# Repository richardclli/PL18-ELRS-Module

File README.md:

[English](README.md) | [中文](README_CN.md)

# Flysky PL18 ExpressLRS TX Module

A DIY internal ExpressLRS transmitter module for the Flysky Paladin PL18 radio, repurposing the stock FRM301 module's casing and RF module.

## Overview

The Flysky PL18 ships with the FRM301 external TX module. This project replaces the FRM301's internal PCB with a custom carrier board that combines a **Waveshare ESP32-S3-Tiny** as the protocol bridge and the FRM301's **HF200 RF module** as the 2.4GHz ExpressLRS frontend. The result is a fully-featured, drop-in ExpressLRS transmitter module that fits the existing module bay and communicates with the radio over its 5-pin SPORT port.

### Features

- Drop-in replacement for the FRM301 module — reuses the original casing
- Waveshare ESP32-S3-Tiny running ExpressLRS firmware
- HF200 2.4GHz RF module with antenna diversity switching
- Dual WS2812B-2020 RGB status LEDs
- Boot button for easy firmware flashing
- Powered entirely from the radio's 5V rail

## Photos

## Bill of Materials

| Ref | Part | Qty | Notes |
|-----|------|:---:|-------|
| — | PL18-ELRS PCB | 1 | Order using the Gerber files in this repo |
| — | FRM301 donor module | 1 | Harvest the HF200 RF module and the plastic casing |
| U1 | Waveshare ESP32-S3-Tiny | 1 | [Product page](https://www.waveshare.com/esp32-s3-tiny.htm) |
| U2 | HF200 RF module | 1 | Desoldered from the FRM301 |
| D1, D2 | WS2812B-2020 | 2 | 2.0×2.0mm PLCC4 package RGB LED |
| R1, R2 | 10kΩ 0603 resistor | 2 | |
| SW1 | KMR2 tactile switch | 1 | 3.2×4.2mm |
| J1 | 5-pin 2.54mm male header | 1 | DS-B01F-A-S2 or equivalent |

## Pinout

### PL18 Connector (J1)

| Pin | Signal | ESP32-S3 GPIO | Description |
|:---:|:------:|:-------------:|-------------|
| 1 | SPORT | IO04 | S.Port (bidirectional CRSF protocol) |
| 2 | GND | — | Ground |
| 3 | +5V | — | 5V power input from radio |
| 4 | NC | — | Not connected |
| 5 | NC | — | Not connected |

### ESP32-S3 to HF200 RF Module

| ESP32-S3 GPIO | HF200 Pin | Function |
|:-------------:|:---------:|----------|
| IO04 | — | SPORT (to PL18 connector) |
| IO06 | TXEN | TX enable |
| IO07 | RXEN | RX enable |
| IO08 | DI01 | Bidirectional data |
| IO09 | BUSY | Busy status (input) |
| IO10 | SPI_NSS | SPI chip select |
| IO11 | SPI_MOSI | SPI MOSI |
| IO12 | SPI_CLK | SPI clock |
| IO13 | SPI_MISO | SPI MISO |
| IO14 | RESET | HF200 reset |
| IO15 | L_ANT_SW | Left antenna switch |
| IO16 | R_ANT_SW | Right antenna switch |
| IO17 | SW1 | Boot button (active low) |
| IO18 | D1 DIN | WS2812B LED data line |

### Power

| Rail | Source | Supplies |
|------|--------|----------|
| +5V | PL18 connector (J1) | ESP32-S3-Tiny (U1), HF200 (U2) |
| +3V3 | ESP32-S3 internal regulator | WS2812B LEDs (D1, D2), L_POWER pull-up (R2) |

## Schematic & PCB

The PCB design was created in **KiCad 10.0**.

- **Layers:** 2-layer FR4, 1.6mm thickness
- **Copper:** 35μm (1oz)
- **Surface finish:** HASL or ENIG
- **Board shape:** Custom outline matching the FRM301 internal cavity

### KiCad project files

| File | Description |
|------|-------------|
| `PL18_ELRS.kicad_pro` | KiCad project file |
| `PL18_ELRS.kicad_sch` | Schematic |
| `PL18_ELRS.kicad_pcb` | PCB layout |
| `Multi.kicad_sym` | Custom symbol library |
| `Multi.pretty/` | Custom footprint library |

The custom footprints include the `WS_ESP32S3_Tiny` (23-pin SMT module) and `HF200-SMT` (22-pin RF module) footprints matched to the donor parts.

## Assembly

1. **Harvest the HF200.** Open the FRM301 module and carefully desolder the HF200 RF module from the original PCB. Set the plastic casing aside for later use.
2. **Solder the HF200 (U2).** Mount the HF200 module on the **back side** of the PL18-ELRS PCB at the U2 footprint.
3. **Solder the ESP32-S3-Tiny (U1).** Mount on the **front side** at the U1 footprint.
4. **Solder passives and LEDs.** Place R1, R2 (10kΩ 0603), D1, D2 (WS2812B-2020), and SW1 (KMR2 switch) on the **front side**.
5. **Solder the header (J1).** Mount the 5-pin male header on the **back side**, ensuring the pins face toward the rear of the module for proper alignment with the PL18 bay connector.
6. **Fit into the casing.** Insert the assembled PCB into the salvaged FRM301 plastic casing.

## Firmware

The ExpressLRS target definition for the Flysky PL18 is maintained at:

**[github.com/richardclli/ELRS-targets](https://github.com/richardclli/ELRS-targets)**

### Flashing

1. Use the ExpressLRS Configurator and select the **Flysky PL18** target.
2. Connect the ESP32-S3-Tiny via USB to your computer.
3. Hold the boot button (SW1) while applying power (or while connecting USB).
4. Flash the firmware using the configurator.

After flashing, configure ExpressLRS to use the **SPORT** protocol for telemetry.

## Manufacturing

The repository includes a complete set of manufacturing outputs in the root directory:

| File | Description |
|------|-------------|
| `PL18_ELRS-F_Cu.gbr` | Top copper |
| `PL18_ELRS-B_Cu.gbr` | Bottom copper |
| `PL18_ELRS-F_Mask.gbr` | Top solder mask |
| `PL18_ELRS-B_Mask.gbr` | Bottom solder mask |
| `PL18_ELRS-F_Paste.gbr` | Top solder paste |
| `PL18_ELRS-B_Paste.gbr` | Bottom solder paste |
| `PL18_ELRS-F_Silkscreen.gbr` | Top silkscreen |
| `PL18_ELRS-B_Silkscreen.gbr` | Bottom silkscreen |
| `PL18_ELRS-Edge_Cuts.gbr` | Board outline |
| `PL18_ELRS-PTH.drl` | Plated through-hole drill |
| `PL18_ELRS-NPTH.drl` | Non-plated through-hole drill |

To order PCBs, zip all Gerber and drill files and upload to your preferred fab (JLCPCB, PCBWay, etc.) with these specs:

- **Layers:** 2
- **Thickness:** 1.6mm
- **Material:** FR4
- **Copper:** 1oz
- **Surface finish:** HASL (or ENIG for easier hand-soldering)

## License

This project is licensed under the **MIT License** — see the [LICENSE](LICENSE) file for details.

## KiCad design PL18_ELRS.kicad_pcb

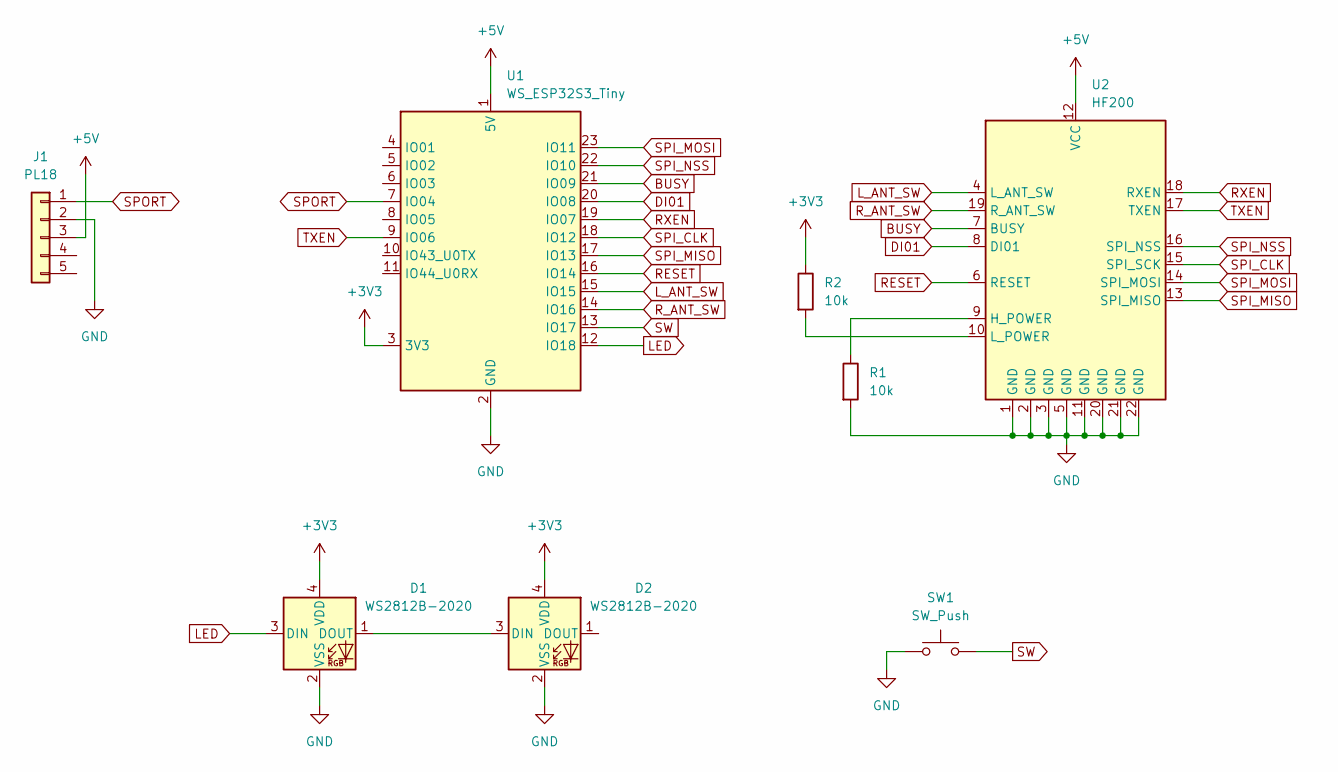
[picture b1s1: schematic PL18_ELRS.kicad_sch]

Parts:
D1, D2: WS2812B-2020; LED_WS2812B-2020_PLCC4_2.0x2.0mm
J1: PL18; DS-B01F-A-S2
R1, R2: 10k; R_0603_1608Metric_Pad0.98x0.95mm_HandSolder
SW1: SW_Push; SW_Push_3.2x4.2
U1: WS_ESP32S3_Tiny
U2: HF200; HF200-SMT

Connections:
+3V3: D1.4 (VDD), D2.4 (VDD), R2.1, U1.3 (3V3)
+5V: J1.3, U1.1 (5V), U2.12 (VCC)
BUSY: U1.21 (IO09), U2.7 (BUSY)
DI01: U1.20 (IO08), U2.8 (DI01)
GND: D1.2 (VSS), D2.2 (VSS), J1.2, R1.2, SW1.1, U1.2 (GND), U2.1 (GND), U2.2 (GND), U2.3 (GND), U2.5 (GND), U2.11 (GND), U2.20 (GND), U2.21 (GND), U2.22 (GND)
LED: D1.3 (DIN), U1.12 (IO18)
L_ANT_SW: U1.15 (IO15), U2.4 (L_ANT_SW)
unnamed: D1.1 (DOUT), D2.3 (DIN)
unnamed: R1.1, U2.9 (H_POWER)
unnamed: R2.2, U2.10 (L_POWER)
RESET: U1.16 (IO14), U2.6 (RESET)
RXEN: U1.19 (IO07), U2.18 (RXEN)
R_ANT_SW: U1.14 (IO16), U2.19 (R_ANT_SW)
SPI_CLK: U1.18 (IO12), U2.15 (SPI_SCK)
SPI_MISO: U1.17 (IO13), U2.13 (SPI_MISO)
SPI_MOSI: U1.23 (IO11), U2.14 (SPI_MOSI)
SPI_NSS: U1.22 (IO10), U2.16 (SPI_NSS)
SPORT: J1.1, U1.7 (IO04)
SW: SW1.2, U1.13 (IO17)
TXEN: U1.9 (IO06), U2.17 (TXEN)

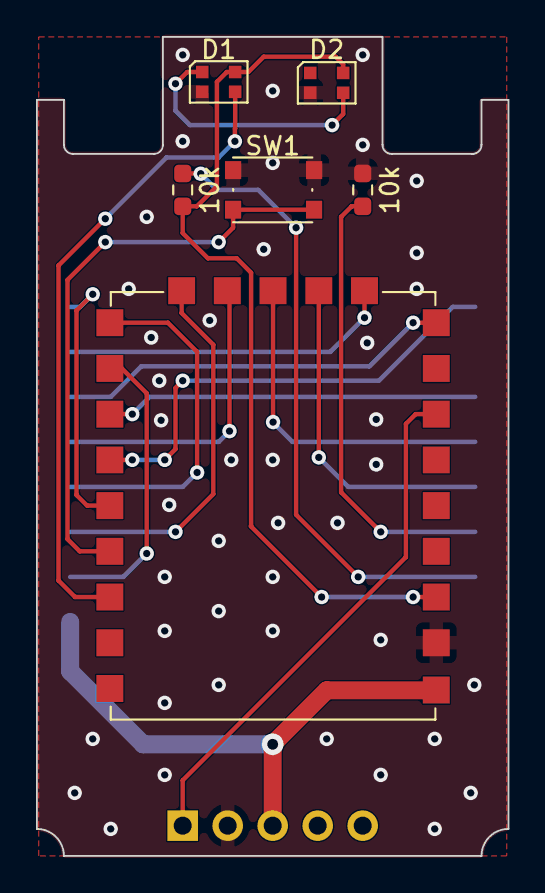
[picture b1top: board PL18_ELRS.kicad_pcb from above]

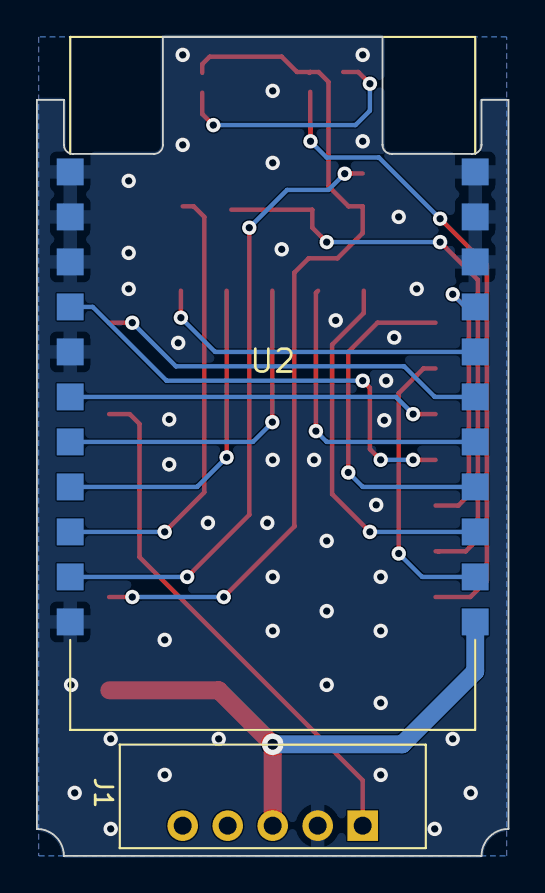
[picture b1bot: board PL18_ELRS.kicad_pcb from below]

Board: 2 copper layers, 26.2 x 45.5 mm, 8 parts (2 on the bottom side), 20 nets.
